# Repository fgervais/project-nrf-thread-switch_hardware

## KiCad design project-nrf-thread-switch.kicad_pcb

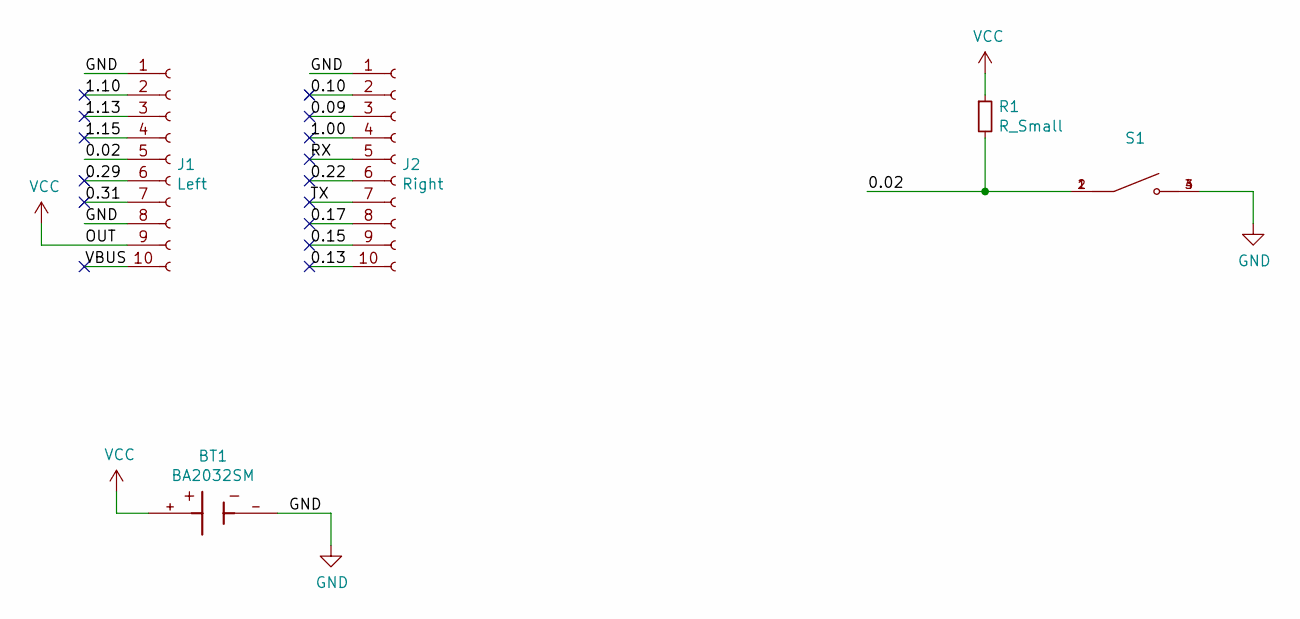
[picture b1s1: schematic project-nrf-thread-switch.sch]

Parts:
BT1: BA2032SM; BAT_BA2032SM; PARTREV K
J1: Left; PinSocket_1x10_P2.54mm_Vertical_SMD_Pin1Right
J2: Right; PinSocket_1x10_P2.54mm_Vertical_SMD_Pin1Right
R1: R_Small; R_0603_1608Metric
S1: 1571563-9; SW_B3FS-1010P

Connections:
/0.02: J1.5, R1.2, S1.1, S1.2
/0.09: J2.3
/0.10: J2.2
/0.13: J2.10
/0.15: J2.9
/0.17: J2.8
/0.22: J2.6
/0.29: J1.6
/0.31: J1.7
/1.00: J2.4
/1.10: J1.2
/1.13: J1.3
/1.15: J1.4
/RX: J2.5
/TX: J2.7
/VBUS: J1.10
GND: BT1.-, J1.1, J1.8, J2.1, S1.3, S1.4
VCC: BT1.+, J1.9, R1.1

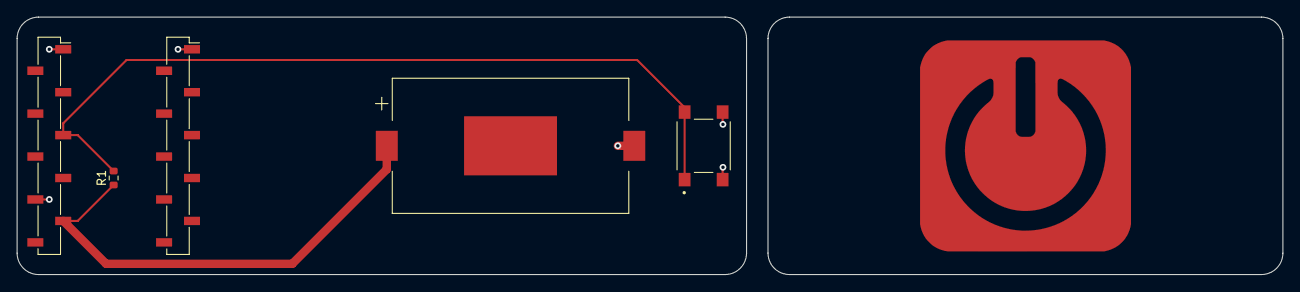
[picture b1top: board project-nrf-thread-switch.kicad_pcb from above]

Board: 2 copper layers, 149.9 x 30.5 mm, 6 parts (0 on the bottom side), 3 nets.

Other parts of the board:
Ref**: Val**; power_sym

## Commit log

2022-03-15 Add library submodule
2022-03-16 Add nrf header to schematic
2022-03-16 Add 8 buttons and the battery
2022-03-16 Keep 5 buttons
2022-03-17 First routing
2022-03-18 Add power_sym
2022-03-18 Save power_sym svg
2022-03-18 Add previous commit version
2022-03-24 Add B3FS-1010
2022-03-25 Single button with header footprint fix
2022-03-26 Routing done
2022-03-26 Move pull-up
2022-03-26 Make track slimmer
2022-05-04 Use https url for kicad library submodule
2023-02-17 Add cardboard design files
2023-02-25 Change to FreeCAD modeling
2023-02-25 Remove previous design
    This one had some double lines and so was refused by ponoko.
2023-02-25 Add freecad tech drawing
2023-02-25 Move spacer a 1mm to the left
2023-02-25 Export design to DXF
2023-02-27 Ignore FreeCAD backup file
2023-03-19 cardboard button: Add README
